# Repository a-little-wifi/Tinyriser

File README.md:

# TinyRiser
Cooler/cuter riser for Lenovo 8th/9th gen Tiny5 PCs

Exposes the x8 and x4 PCIe links in the riser slot, in the form of a PCIe x16 slot and an m.2 slot.

The x8 link comes from the CPU and was meant for GPU equipped models, while the x4 link comes from the PCH and was meant for the Thunderbolt and NIC equipped models. Lenovo made two different risers for these configurations, only using one link at a time, but this riser gives you both PCIe links at once! The two links are completely independent and are able to function at the same time.

Using this riser, you can install a low profile PCIe card just as you can with the stock risers, and add an extra M.2 NVMe SSD in addition to the onboard ones. The SSD is tucked away near the front of the machine, plugged into a right angle M-key M.2 slot that holds the SSD firmly in place. Due to an unfortunate non-removable standoff placement on the motherboard, only 2230, 2242 and 2260 size SSDs fit comfortably. It is possible to get a 2280 drive to fit if you try hard enough, but the fit will be suboptimal.

Doesn't require any modifications to the motherboard, just works plug and play (no bifurcation/lane reversal).

I've successfully tested this riser on my own M720q where it works 100% perfectly with x1, x4, x8 and x16 cards, and it will work just as well on the other machines that share this motherboard, the M920q, M920x and P330 Tiny.

Note that the M.2 slot only supports PCIe NVMe M-key or B+M-key drives, not SATA ones.

The v2 design includes a fan header that can be used in multiple ways:

- 12V no PWM
- 12V with PWM
- Voltage controlled speed

The last 2 modes require some kind of fan controller module plugged into the provided header. This has not been designed yet, but the possibility exists.

> Front side render of the PCB. I don't have a 3D model for the m.2 slot but you can see the footprint for it

> Back side render of the PCB.

> Front of it but in real life

> Back of it but also in real life

Compatible with M720q, M920q, M920x and P330 Tiny, as well as the NEC rebranded versions of those.  
**Don't stick it in an M910x or P320 Tiny, it will physically fit but the pinout is not compatible.**

Currently in version 2.1

## Parts list:
| part                    | Qty | model                     | link                                                                                     |
|-------------------------|-----|---------------------------|------------------------------------------------------------------------------------------|
| PCIe slot               | 1   | UMAX 3183-10203P1T        | https://www.lcsc.com/product-detail/Card-Edge-Connectors_UMAX-3183-10203P1T_C404116.html |
| Vertical M-key slot     | 1   | HOAUC HYCW19M-05NGFF-530B | https://www.lcsc.com/product-detail/C41430861.html                                       |
| Alt Vertical M-key slot | 0   | Lotes APCI0110-P001A      | (available on aliexpress)                                                                |
| Screwpost               | 1   | YIYUAN SMTSOM340BTR       | https://www.lcsc.com/product-detail/Other-nuts_YIYUAN-SMTSOM340BTR_C5301786.html         |
| 10uF 0603 capacitor     | 2   |                           |                                                                                          |
| 100nF 0603 capacitor    | 1   |                           |                                                                                          |
| 4-pin right angle header| 1   |                           |                                                                                          |
| 5.1kΩ 0603 resistor     | 1   |                           |                                                                                          |
| 0603 LED (pick a color) | 1   |                           |                                                                                          |

## JLC PCB ordering details:

Please use the files from the v2.1 release, the main repo might be in the middle of version changes

> Screenshot of the JLC PCB order settings used for TinyRiser

https://github.com/a-little-wifi/Tinyriser/assets/139929586/086969f3-38e6-4d3a-b0c4-e65df9add474  
> unmute it

# Attribution
If you distribute this design or use this design to create a derivative design, you must keep attribution to this original design, in addition to following the terms in the license

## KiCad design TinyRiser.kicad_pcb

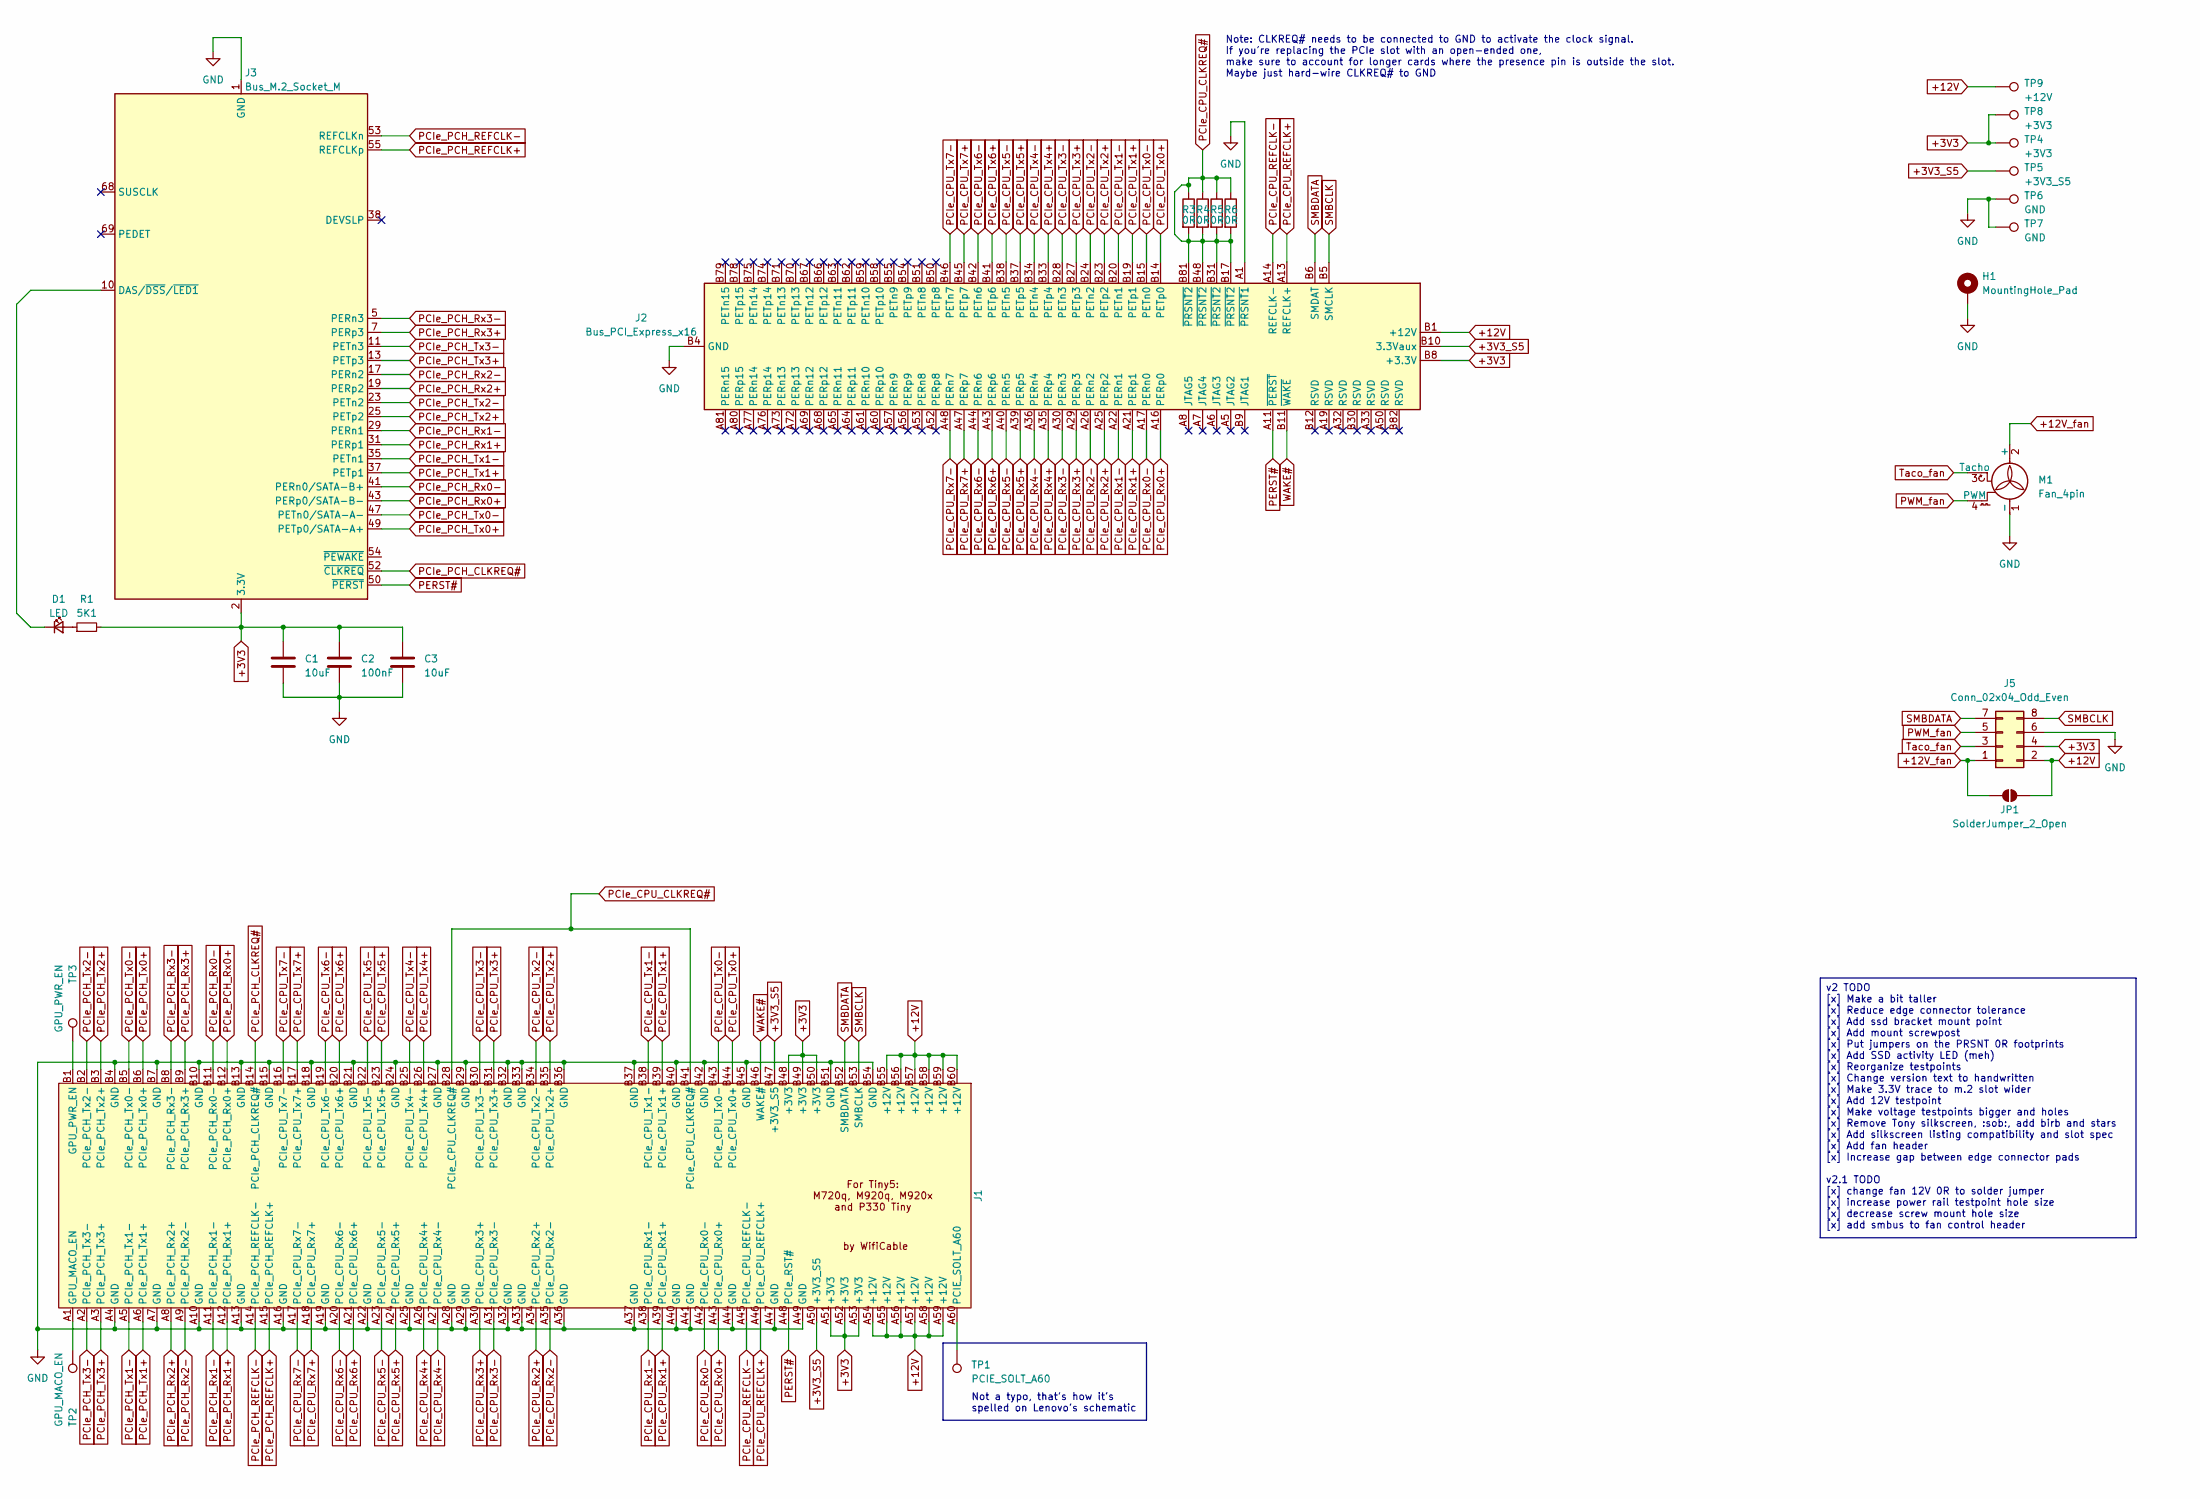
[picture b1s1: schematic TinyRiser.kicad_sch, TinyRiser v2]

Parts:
C1, C3: 10uF; C_0603_1608Metric
C2: 100nF; C_0603_1608Metric
D1: LED; D_0603_1608Metric_Pad1.05x0.95mm_HandSolder
H1: MountingHole_Pad; MountingHole_4.3mm_M4_ISO7380_Pad_TopOnly; LCSC Part C5301786
J1: TinyRiser
J2: Bus_PCI_Express_x16; PCIe_x16_tht; LCSC Part C404116
J3: Bus_M.2_Socket_M; M.2_NGFF_KeyM_H5.3_Vertical; LCSC Part C41430861
J5: Conn_02x04_Odd_Even; PinSocket_2x04_P2.54mm_Horizontal
JP1: SolderJumper_2_Open; SolderJumper-2_P1.3mm_Open_TrianglePad1.0x1.5mm
M1: Fan_4pin; PinHeader_1x04_P2.54mm_Horizontal
R1: 5K1; R_0603_1608Metric_Pad0.98x0.95mm_HandSolder
R3, R4, R5, R6: 0R; R_0603_1608Metric_Pad0.98x0.95mm_HandSolder
TP1: PCIE_SOLT_A60; TestPoint_Pad_D1.0mm
TP2: GPU_MACO_EN; TestPoint_Pad_D1.0mm
TP3: GPU_PWR_EN; TestPoint_Pad_D1.0mm
TP4, TP8: +3V3; TestPoint_THTPad_D1.5mm_Drill0.7mm
TP5: +3V3_S5; TestPoint_THTPad_D1.5mm_Drill0.7mm
TP6, TP7: GND; TestPoint_THTPad_D1.5mm_Drill0.7mm
TP9: +12V; TestPoint_THTPad_D1.5mm_Drill0.7mm

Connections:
+3V3: C1.1, C2.1, C3.1, J1.A51 (+3V3), J1.A52 (+3V3), J1.A53 (+3V3), J1.B48 (+3V3), J1.B49 (+3V3), J1.B50 (+3V3), J2.A9 (+3.3V), J2.A10 (+3.3V), J2.B8 (+3.3V), J3.2 (3.3V), J3.4 (3.3V), J3.12 (3.3V), J3.14 (3.3V), J3.16 (3.3V), J3.18 (3.3V), J3.70 (3.3V), J3.72 (3.3V), J3.74 (3.3V), J5.4, R1.2, TP4.1, TP8.1
+3V3_S5: J1.A50 (+3V3_S5), J1.B47 (+3V3_S5), J2.B10 (3.3Vaux), TP5.1
+12V: J1.A54 (+12V), J1.A55 (+12V), J1.A56 (+12V), J1.A57 (+12V), J1.A58 (+12V), J1.A59 (+12V), J1.B55 (+12V), J1.B56 (+12V), J1.B57 (+12V), J1.B58 (+12V), J1.B59 (+12V), J1.B60 (+12V), J2.A2 (+12V), J2.A3 (+12V), J2.B1 (+12V), J2.B2 (+12V), J2.B3 (+12V), J5.2, JP1.2 (B), TP9.1
+12V_fan: J5.1, JP1.1 (A), M1.2 (+)
GND: C1.2, C2.2, C3.2, H1.1, J1.A4 (GND), J1.A7 (GND), J1.A10 (GND), J1.A13 (GND), J1.A16 (GND), J1.A19 (GND), J1.A22 (GND), J1.A25 (GND), J1.A28 (GND), J1.A29 (GND), J1.A32 (GND), J1.A33 (GND), J1.A36 (GND), J1.A37 (GND), J1.A40 (GND), J1.A41 (GND), J1.A44 (GND), J1.A47 (GND), J1.A49 (GND), J1.B4 (GND), J1.B7 (GND), J1.B10 (GND), J1.B13 (GND), J1.B15 (GND), J1.B18 (GND), J1.B21 (GND), J1.B24 (GND), J1.B27 (GND), J1.B29 (GND), J1.B32 (GND), J1.B33 (GND), J1.B36 (GND), J1.B37 (GND), J1.B40 (GND), J1.B42 (GND), J1.B45 (GND), J1.B51 (GND), J1.B54 (GND), J2.A1 (~PRSNT1), J2.A4 (GND), J2.A12 (GND), J2.A15 (GND), J2.A18 (GND), J2.A20 (GND), J2.A23 (GND), J2.A24 (GND), J2.A27 (GND), J2.A28 (GND), J2.A31 (GND), J2.A34 (GND), J2.A37 (GND), J2.A38 (GND), J2.A41 (GND), J2.A42 (GND), J2.A45 (GND), J2.A46 (GND), J2.A49 (GND), J2.A51 (GND), J2.A54 (GND), J2.A55 (GND), J2.A58 (GND), J2.A59 (GND), J2.A62 (GND), J2.A63 (GND), J2.A66 (GND), J2.A67 (GND), J2.A70 (GND), J2.A71 (GND), J2.A74 (GND), J2.A75 (GND), J2.A78 (GND), J2.A79 (GND), J2.A82 (GND), J2.B4 (GND), J2.B7 (GND), J2.B13 (GND), J2.B16 (GND), J2.B18 (GND), J2.B21 (GND), J2.B22 (GND), J2.B25 (GND), J2.B26 (GND), J2.B29 (GND), J2.B32 (GND), J2.B35 (GND), J2.B36 (GND), J2.B39 (GND), J2.B40 (GND), J2.B43 (GND), J2.B44 (GND), J2.B47 (GND), J2.B49 (GND), J2.B52 (GND), J2.B53 (GND), J2.B56 (GND), J2.B57 (GND), J2.B60 (GND), J2.B61 (GND), J2.B64 (GND), J2.B65 (GND), J2.B68 (GND), J2.B69 (GND), J2.B72 (GND), J2.B73 (GND), J2.B76 (GND), J2.B77 (GND), J2.B80 (GND), J3.1 (GND), J3.3 (GND), J3.9 (GND), J3.15 (GND), J3.21 (GND), J3.27 (GND), J3.33 (GND), J3.39 (GND), J3.45 (GND), J3.51 (GND), J3.57 (GND), J3.71 (GND), J3.73 (GND), J3.75 (GND), J5.6, M1.1 (-), TP6.1, TP7.1
unnamed: D1.2 (A), R1.1
unnamed: D1.1 (K), J3.10 (DAS/~DSS/~LED1)
unnamed: J1.A1 (GPU_MACO_EN), TP2.1
unnamed: J1.B1 (GPU_PWR_EN), TP3.1
unnamed: J1.A60 (PCIE_SOLT_A60), TP1.1
PCIe_CPU_CLKREQ#: J1.B28 (PCIe_CPU_CLKREQ#), J1.B41 (PCIe_CPU_CLKREQ#), J2.B17 (~PRSNT2), J2.B31 (~PRSNT2), J2.B48 (~PRSNT2), J2.B81 (~PRSNT2), R3.1, R3.2, R4.1, R4.2, R5.1, R5.2, R6.1, R6.2
PCIe_CPU_REFCLK+: J1.A46 (PCIe_CPU_REFCLK+), J2.A13 (REFCLK+)
PCIe_CPU_REFCLK-: J1.A45 (PCIe_CPU_REFCLK-), J2.A14 (REFCLK-)
PCIe_CPU_Rx0+: J1.A43 (PCIe_CPU_Rx0+), J2.A16 (PERp0)
PCIe_CPU_Rx0-: J1.A42 (PCIe_CPU_Rx0-), J2.A17 (PERn0)
PCIe_CPU_Rx1+: J1.A39 (PCIe_CPU_Rx1+), J2.A21 (PERp1)
PCIe_CPU_Rx1-: J1.A38 (PCIe_CPU_Rx1-), J2.A22 (PERn1)
PCIe_CPU_Rx2+: J1.A34 (PCIe_CPU_Rx2+), J2.A25 (PERp2)
PCIe_CPU_Rx2-: J1.A35 (PCIe_CPU_Rx2-), J2.A26 (PERn2)
PCIe_CPU_Rx3+: J1.A30 (PCIe_CPU_Rx3+), J2.A29 (PERp3)
PCIe_CPU_Rx3-: J1.A31 (PCIe_CPU_Rx3-), J2.A30 (PERn3)
PCIe_CPU_Rx4+: J1.A26 (PCIe_CPU_Rx4+), J2.A35 (PERp4)
PCIe_CPU_Rx4-: J1.A27 (PCIe_CPU_Rx4-), J2.A36 (PERn4)
PCIe_CPU_Rx5+: J1.A24 (PCIe_CPU_Rx5+), J2.A39 (PERp5)
PCIe_CPU_Rx5-: J1.A23 (PCIe_CPU_Rx5-), J2.A40 (PERn5)
PCIe_CPU_Rx6+: J1.A21 (PCIe_CPU_Rx6+), J2.A43 (PERp6)
PCIe_CPU_Rx6-: J1.A20 (PCIe_CPU_Rx6-), J2.A44 (PERn6)
PCIe_CPU_Rx7+: J1.A18 (PCIe_CPU_Rx7+), J2.A47 (PERp7)
PCIe_CPU_Rx7-: J1.A17 (PCIe_CPU_Rx7-), J2.A48 (PERn7)
PCIe_CPU_Tx0+: J1.B44 (PCIe_CPU_Tx0+), J2.B14 (PETp0)
PCIe_CPU_Tx0-: J1.B43 (PCIe_CPU_Tx0-), J2.B15 (PETn0)
PCIe_CPU_Tx1+: J1.B39 (PCIe_CPU_Tx1+), J2.B19 (PETp1)
PCIe_CPU_Tx1-: J1.B38 (PCIe_CPU_Tx1-), J2.B20 (PETn1)
PCIe_CPU_Tx2+: J1.B35 (PCIe_CPU_Tx2+), J2.B23 (PETp2)
PCIe_CPU_Tx2-: J1.B34 (PCIe_CPU_Tx2-), J2.B24 (PETn2)
PCIe_CPU_Tx3+: J1.B31 (PCIe_CPU_Tx3+), J2.B27 (PETp3)
PCIe_CPU_Tx3-: J1.B30 (PCIe_CPU_Tx3-), J2.B28 (PETn3)
PCIe_CPU_Tx4+: J1.B26 (PCIe_CPU_Tx4+), J2.B33 (PETp4)
PCIe_CPU_Tx4-: J1.B25 (PCIe_CPU_Tx4-), J2.B34 (PETn4)
PCIe_CPU_Tx5+: J1.B23 (PCIe_CPU_Tx5+), J2.B37 (PETp5)
PCIe_CPU_Tx5-: J1.B22 (PCIe_CPU_Tx5-), J2.B38 (PETn5)
PCIe_CPU_Tx6+: J1.B20 (PCIe_CPU_Tx6+), J2.B41 (PETp6)
PCIe_CPU_Tx6-: J1.B19 (PCIe_CPU_Tx6-), J2.B42 (PETn6)
PCIe_CPU_Tx7+: J1.B17 (PCIe_CPU_Tx7+), J2.B45 (PETp7)
PCIe_CPU_Tx7-: J1.B16 (PCIe_CPU_Tx7-), J2.B46 (PETn7)
PCIe_PCH_CLKREQ#: J1.B14 (PCIe_PCH_CLKREQ#), J3.52 (~CLKREQ)
PCIe_PCH_REFCLK+: J1.A15 (PCIe_PCH_REFCLK+), J3.55 (REFCLKp)
PCIe_PCH_REFCLK-: J1.A14 (PCIe_PCH_REFCLK-), J3.53 (REFCLKn)
PCIe_PCH_Rx0+: J1.B12 (PCIe_PCH_Rx0+), J3.43 (PERp0/SATA-B-)
PCIe_PCH_Rx0-: J1.B11 (PCIe_PCH_Rx0-), J3.41 (PERn0/SATA-B+)
PCIe_PCH_Rx1+: J1.A12 (PCIe_PCH_Rx1+), J3.31 (PERp1)
PCIe_PCH_Rx1-: J1.A11 (PCIe_PCH_Rx1-), J3.29 (PERn1)
PCIe_PCH_Rx2+: J1.A8 (PCIe_PCH_Rx2+), J3.19 (PERp2)
PCIe_PCH_Rx2-: J1.A9 (PCIe_PCH_Rx2-), J3.17 (PERn2)
PCIe_PCH_Rx3+: J1.B9 (PCIe_PCH_Rx3+), J3.7 (PERp3)
PCIe_PCH_Rx3-: J1.B8 (PCIe_PCH_Rx3-), J3.5 (PERn3)
PCIe_PCH_Tx0+: J1.B6 (PCIe_PCH_Tx0+), J3.49 (PETp0/SATA-A+)
PCIe_PCH_Tx0-: J1.B5 (PCIe_PCH_Tx0-), J3.47 (PETn0/SATA-A-)
PCIe_PCH_Tx1+: J1.A6 (PCIe_PCH_Tx1+), J3.37 (PETp1)
PCIe_PCH_Tx1-: J1.A5 (PCIe_PCH_Tx1-), J3.35 (PETn1)
PCIe_PCH_Tx2+: J1.B3 (PCIe_PCH_Tx2+), J3.25 (PETp2)
PCIe_PCH_Tx2-: J1.B2 (PCIe_PCH_Tx2-), J3.23 (PETn2)
PCIe_PCH_Tx3+: J1.A3 (PCIe_PCH_Tx3+), J3.13 (PETp3)
PCIe_PCH_Tx3-: J1.A2 (PCIe_PCH_Tx3-), J3.11 (PETn3)
PERST#: J1.A48 (PCIe_RST#), J2.A11 (~PERST), J3.50 (~PERST)
PWM_fan: J5.5, M1.4 (PWM)
SMBCLK: J1.B53 (SMBCLK), J2.B5 (SMCLK), J5.8
SMBDATA: J1.B52 (SMBDATA), J2.B6 (SMDAT), J5.7
Taco_fan: J5.3, M1.3 (Tacho)
WAKE#: J1.B46 (WAKE#), J2.B11 (~WAKE)

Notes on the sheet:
Not a typo, that's how it's spelled on Lenovo's schematic
Note: CLKREQ# needs to be connected to GND to activate the clock signal. If you're replacing the PCIe slot with an open-ended one, make sure to account for longer cards where the presence pin is outside the slot. Maybe just hard-wire CLKREQ# to GND
v2 TODO [x] Make a bit taller [x] Reduce edge connector tolerance [x] Add ssd bracket mount point [x] Add mount screwpost [x] Put jumpers on the PRSNT 0R footprints [x] Add SSD activity LED (meh) [x] Reorganize testpoints [x] Change version text to handwritten [x] Make 3.3V trace to m.2 slot wider 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

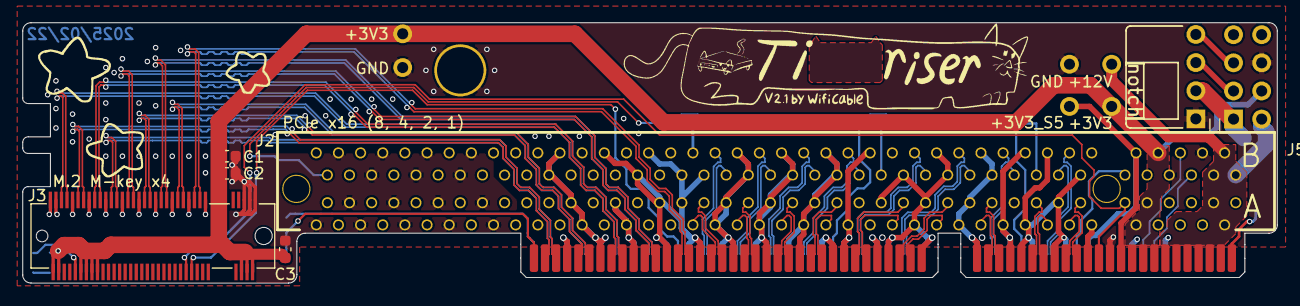
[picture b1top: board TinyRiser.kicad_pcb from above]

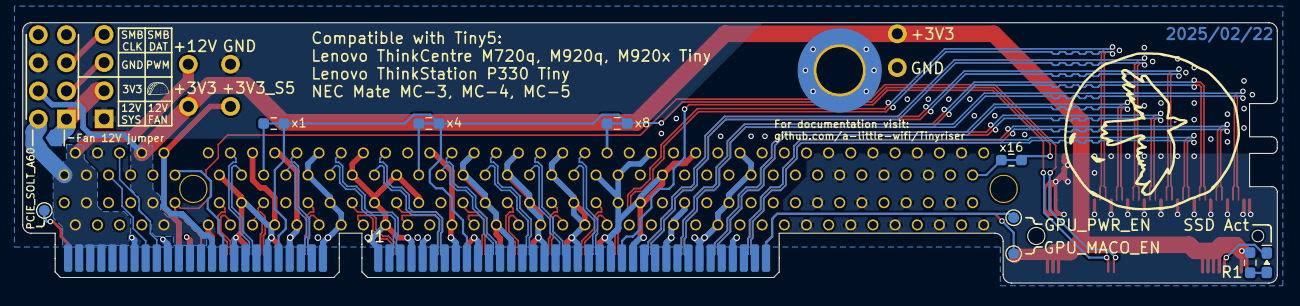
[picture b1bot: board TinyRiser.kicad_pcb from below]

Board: 4 copper layers, 113.2 x 23.5 mm, 25 parts (12 on the bottom side), 70 nets.

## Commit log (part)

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2024-03-05 Added description to readme
2024-03-05 Added version note to readme
2024-03-06 Added long description and images to readme
2024-03-06 Added lock files to gitignore....
2024-03-06 removed lock fiiles
2024-04-11 Upgraded to Kicad 8, Changed compatibility text, changed mount bracket slots, updated readme
2024-04-11 Updated board pictures
2024-04-11 Added remark about bifurcation/lane reversal to readme
2024-04-11 Don't need round tracks config in here lol
2024-04-11 Updated schematic symbol text (and also sch to KiCad 8 ig lol)
2024-05-03 Adding fan header (unfinished)
2024-05-03 Mostly finished fan connector implementation
2024-05-09 swapped fan header for right angle pin header
2024-05-15 Finished fan header implementation
    Somehow it doesn't feel like it's done but it is???
2024-05-15 updated pcb datecode lol
    why do i even put that on there
2024-05-15 Moved some silkscreen
2024-05-15 Moved some more silkscreen
2024-05-15 Moved a trace
    so many smol changes lol
2024-05-15 Ticked off completed todo list items, also the edge connector footprint was changed in an earlier commit but i forgot to mention it
2024-05-15 Corrected weird 3.3V plane setting
2024-05-15 Fixed minor DRC errors
2024-05-15 long
2024-05-15 unlong
    definitely not shitposting in my git repo
2024-05-15 merged redundant keepout zones
2024-06-13 a little prettier
2024-06-13 Adjusted edge footprint line width
2024-06-13 Slight silkscreen adjustments
2024-06-13 Fixed edge footprint origin
2024-06-24 Remove old pictures
2024-06-24 2015
2024-07-13 Added pictures of v2 pcb assembled
2024-09-06 Moved fan header 3d model to represent real position
2024-10-21 Added M-key part number to readme
2024-11-14 Updated readme because v2 is also tested
2025-01-27 Changed fan power 0R to solder jumper for easier assembly (v2.1) and added pcb ordering information
2025-01-27 updated readme for pcb order details image
2025-01-27 Increased power rail testpoint hole size and decreased screwpost hole size for better fit
2025-01-27 moved ssd power trace a little
2025-01-27 added note about using v2 release for pcb ordering
2025-01-29 Added v2.1 todo list to schematic
2025-02-07 Added clearer component list to readme
2025-02-18 clarified led polarity on silkscreen
2025-02-18 starting to add smbus to fan control header
2025-02-21 Finished adding smbus to fan control header
2025-02-21 small silkscreen changes for 12V jumper
2025-02-22 Changed logo to v2.1
2025-02-22 Readme fixes, v2.1 might be done?
2025-03-12 Added alternative version with ssd led on the front for pcba
2025-04-14 Adjusted frontled via size, trace routing and resistor placement
    wow I really did that quick and sloppily last time. I still don't like this version, it looks weird, but it's a little better now at least. Sorry to anyone who already had a stencil made for the prev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
2025-04-14 Clarified alternative m.2 slot footprint compatibility
2025-04-15 Removed link to alternative M.2 slot with different footprint to avoid confusion
2025-05-23 Added license
2025-05-23 Added attribution notice
2025-05-23 Added some notes
2025-06-03 Added note to frontled version too
2025-06-09 gerber export stuff
2025-10-02 Changed readme for v2.1 release
    maybe should have done that before making the release lol, oh well
2026-04-29 Updated parts list
    Added lcsc option for M.2 slot
